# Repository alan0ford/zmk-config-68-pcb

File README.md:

## PCB 68 keyboard
PCB bluetooth mechanical keyboard.

- Case: in plywood handmade [(photo)](https://i.imgur.com/p45XYWJ.jpg)
- [PCB](https://imgur.com/a/tlV6TRd)
- Keycpas: CRP-X Parallel Worlds
- Switches: WS Jade POM linear 50 g
- MCU: SuperMini NRF52580 [(nice!nano compatible)](http://wiki.icbbuy.com/doku.php?id=developmentboard:nrf52840)
- Soundcheck ([here](https://vimeo.com/914201447?share=copy))

Inspired by Ikki 68:

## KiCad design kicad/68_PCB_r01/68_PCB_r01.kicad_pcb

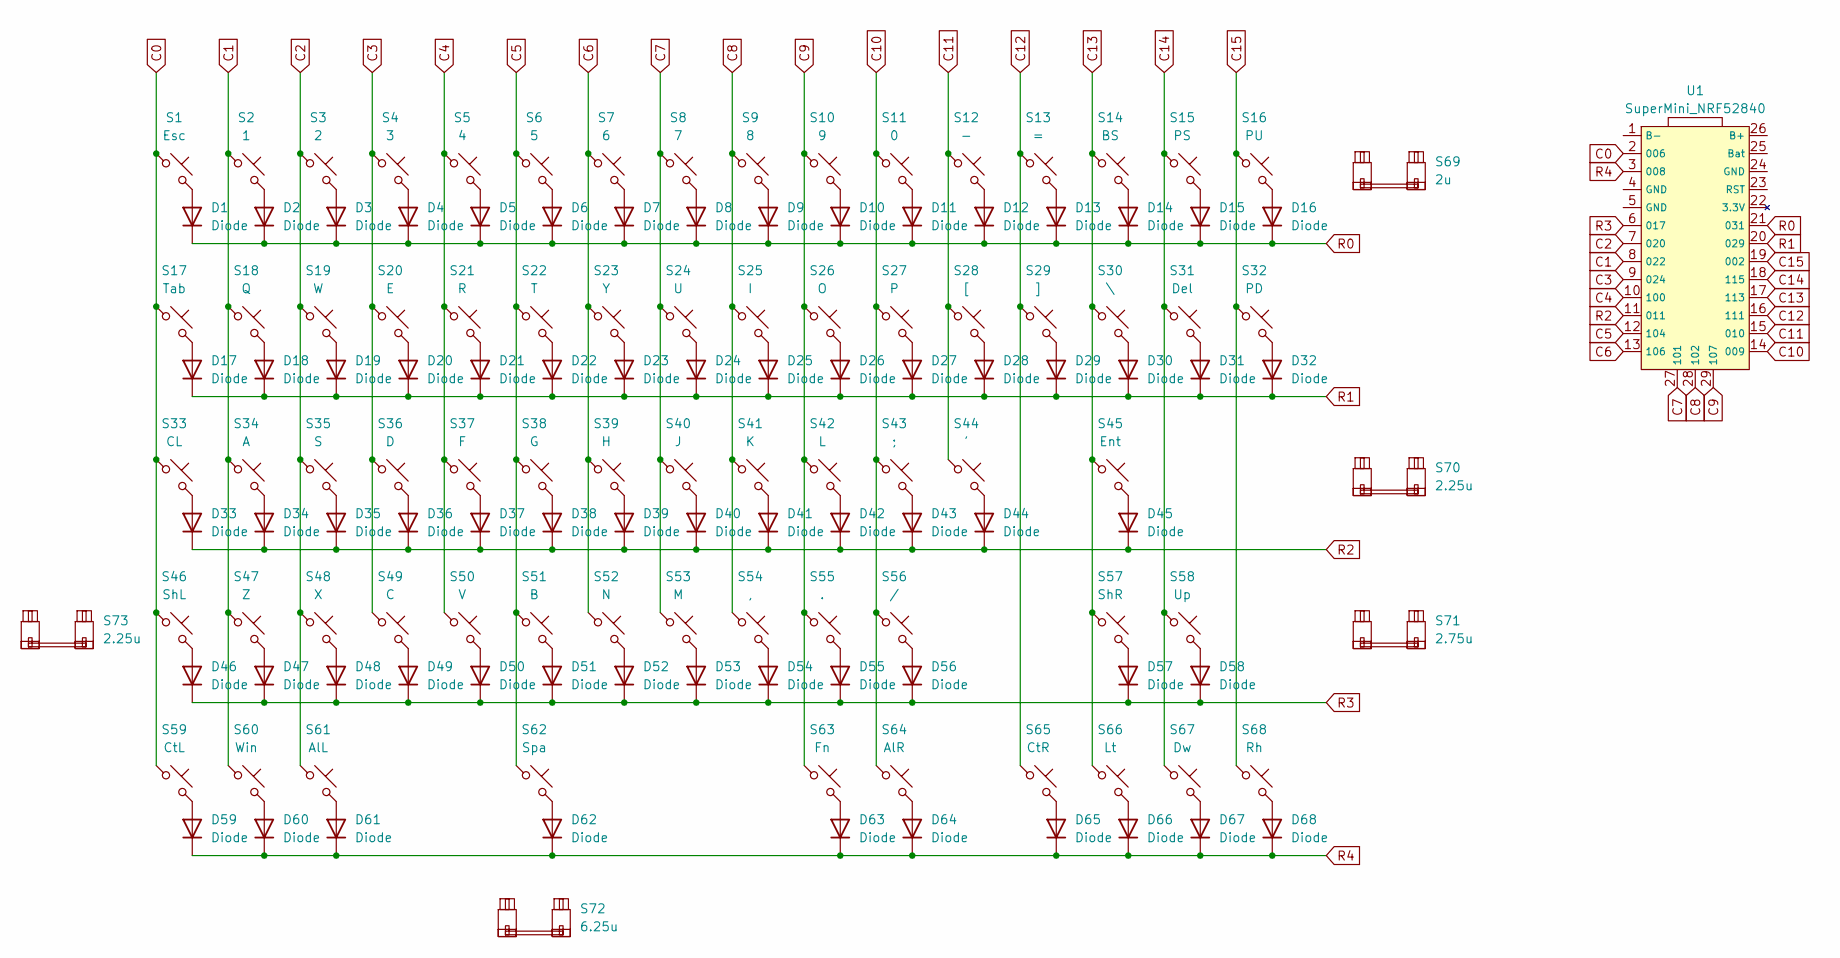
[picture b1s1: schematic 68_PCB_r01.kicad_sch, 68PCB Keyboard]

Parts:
D1, D2, D3, D4, D5, D6, D7, D8, D9, D10, D11, D12, D13, D14, D15, D16, D17, D18, D19, D20, D21, D22, D23, D24, D25, D26, D27, D28, D29, D30, D31, D32, D33, D34, D35, D36, D37, D38, D39, D40, D41, D42, D43, D44, D45, D46, D47, D48, D49, D50, D51, D52, D53, D54, D55, D56, D57, D58, D59, D60, D61, D62, D63, D64, D65, D66, D67, D68: Diode; Diode_DO-35
S1: Esc; MX_PCB_1.00u
S2: 1; MX_PCB_1.00u
S3: 2; MX_PCB_1.00u
S4: 3; MX_PCB_1.00u
S5: 4; MX_PCB_1.00u
S6: 5; MX_PCB_1.00u
S7: 6; MX_PCB_1.00u
S8: 7; MX_PCB_1.00u
S9: 8; MX_PCB_1.00u
S10: 9; MX_PCB_1.00u
S11: 0; MX_PCB_1.00u
S12: -; MX_PCB_1.00u
S13: =; MX_PCB_1.00u
S14: BS; MX_PCB_2.00u
S15: PS; MX_PCB_1.00u
S16: PU; MX_PCB_1.00u
S17: Tab; MX_PCB_1.50u
S18: Q; MX_PCB_1.00u
S19: W; MX_PCB_1.00u
S20: E; MX_PCB_1.00u
S21: R; MX_PCB_1.00u
S22: T; MX_PCB_1.00u
S23: Y; MX_PCB_1.00u
S24: U; MX_PCB_1.00u
S25: I; MX_PCB_1.00u
S26: O; MX_PCB_1.00u
S27: P; MX_PCB_1.00u
S28: [; MX_PCB_1.00u
S29: ]; MX_PCB_1.00u
S30: \; MX_PCB_1.50u
S31: Del; MX_PCB_1.00u
S32: PD; MX_PCB_1.00u
S33: CL; MX_PCB_1.75u
S34: A; MX_PCB_1.00u
S35: S; MX_PCB_1.00u
S36: D; MX_PCB_1.00u
S37: F; MX_PCB_1.00u
S38: G; MX_PCB_1.00u
S39: H; MX_PCB_1.00u
S40: J; MX_PCB_1.00u
S41: K; MX_PCB_1.00u
S42: L; MX_PCB_1.00u
S43: ;; MX_PCB_1.00u
S44: '; MX_PCB_1.00u
S45: Ent; MX_PCB_2.25u
S46: ShL; MX_PCB_2.25u
S47: Z; MX_PCB_1.00u
S48: X; MX_PCB_1.00u
S49: C; MX_PCB_1.00u
S50: V; MX_PCB_1.00u
S51: B; MX_PCB_1.00u
S52: N; MX_PCB_1.00u
S53: M; MX_PCB_1.00u
S54: ,; MX_PCB_1.00u
S55: .; MX_PCB_1.00u
S56: /; MX_PCB_1.00u
S57: ShR; MX_PCB_2.75u
S58: Up; MX_PCB_1.00u
S59: CtL; MX_PCB_1.25u
S60: Win; MX_PCB_1.25u
S61: AlL; MX_PCB_1.25u
S62: Spa; MX_PCB_6.25u
S63: Fn; MX_PCB_1.25u
S64: AlR; MX_PCB_1.25u
S65: CtR; MX_PCB_1.25u
S66: Lt; MX_PCB_1.00u
S67: Dw; MX_PCB_1.00u
S68: Rh; MX_PCB_1.00u
S69: 2u; STAB_MX_2u
S70, S73: 2.25u; STAB_MX_2.25u
S71: 2.75u; STAB_MX_2.75u
S72: 6.25u; STAB_MX_6.25u
U1: SuperMini_NRF52840; SuperMini NRF52840

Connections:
C0: S1.1, S17.1, S33.1, S46.1, S59.1, U1.2 (006)
C1: S2.1, S18.1, S34.1, S47.1, S60.1, U1.8 (022)
C2: S3.1, S19.1, S35.1, S48.1, S61.1, U1.7 (020)
C3: S4.1, S20.1, S36.1, S49.1, U1.9 (024)
C4: S5.1, S21.1, S37.1, S50.1, U1.10 (100)
C5: S6.1, S22.1, S38.1, S51.1, S62.1, U1.12 (104)
C6: S7.1, S23.1, S39.1, S52.1, U1.13 (106)
C7: S8.1, S24.1, S40.1, S53.1, U1.27 (101)
C8: S9.1, S25.1, S41.1, S54.1, U1.28 (102)
C9: S10.1, S26.1, S42.1, S55.1, S63.1, U1.29 (107)
C10: S11.1, S27.1, S43.1, S56.1, S64.1, U1.14 (009)
C11: S12.1, S28.1, S44.1, U1.15 (010)
C12: S13.1, S29.1, S65.1, U1.16 (111)
C13: S14.1, S30.1, S45.1, S57.1, S66.1, U1.17 (113)
C14: S15.1, S31.1, S58.1, S67.1, U1.18 (115)
C15: S16.1, S32.1, S68.1, U1.19 (002)
unnamed: D1.2 (A), S1.2
unnamed: D2.2 (A), S2.2
unnamed: D3.2 (A), S3.2
unnamed: D4.2 (A), S4.2
unnamed: D5.2 (A), S5.2
unnamed: D6.2 (A), S6.2
unnamed: D7.2 (A), S7.2
unnamed: D8.2 (A), S8.2
unnamed: D9.2 (A), S9.2
unnamed: D10.2 (A), S10.2
unnamed: D11.2 (A), S11.2
unnamed: D12.2 (A), S12.2
unnamed: D13.2 (A), S13.2
unnamed: D14.2 (A), S14.2
unnamed: D15.2 (A), S15.2
unnamed: D16.2 (A), S16.2
unnamed: D17.2 (A), S17.2
unnamed: D18.2 (A), S18.2
unnamed: D19.2 (A), S19.2
unnamed: D20.2 (A), S20.2
unnamed: D21.2 (A), S21.2
unnamed: D22.2 (A), S22.2
unnamed: D23.2 (A), S23.2
unnamed: D24.2 (A), S24.2
unnamed: D25.2 (A), S25.2
unnamed: D26.2 (A), S26.2
unnamed: D27.2 (A), S27.2
unnamed: D28.2 (A), S28.2
unnamed: D29.2 (A), S29.2
unnamed: D30.2 (A), S30.2
unnamed: D31.2 (A), S31.2
unnamed: D32.2 (A), S32.2
unnamed: D33.2 (A), S33.2
unnamed: D34.2 (A), S34.2
unnamed: D35.2 (A), S35.2
unnamed: D36.2 (A), S36.2
unnamed: D37.2 (A), S37.2
unnamed: D38.2 (A), S38.2
unnamed: D39.2 (A), S39.2
unnamed: D40.2 (A), S40.2
unnamed: D41.2 (A), S41.2
unnamed: D42.2 (A), S42.2
unnamed: D43.2 (A), S43.2
unnamed: D44.2 (A), S44.2
unnamed: D45.2 (A), S45.2
unnamed: D46.2 (A), S46.2
unnamed: D47.2 (A), S47.2
unnamed: D48.2 (A), S48.2
unnamed: D49.2 (A), S49.2
unnamed: D50.2 (A), S50.2
unnamed: D51.2 (A), S51.2
unnamed: D52.2 (A), S52.2
unnamed: D53.2 (A), S53.2
unnamed: D54.2 (A), S54.2
unnamed: D55.2 (A), S55.2
unnamed: D56.2 (A), S56.2
unnamed: D57.2 (A), S57.2
unnamed: D58.2 (A), S58.2
unnamed: D59.2 (A), S59.2
unnamed: D60.2 (A), S60.2
unnamed: D61.2 (A), S61.2
unnamed: D62.2 (A), S62.2
unnamed: D63.2 (A), S63.2
unnamed: D64.2 (A), S64.2
unnamed: D65.2 (A), S65.2
unnamed: D66.2 (A), S66.2
unnamed: D67.2 (A), S67.2
unnamed: D68.2 (A), S68.2
R0: D1.1 (K), D2.1 (K), D3.1 (K), D4.1 (K), D5.1 (K), D6.1 (K), D7.1 (K), D8.1 (K), D9.1 (K), D10.1 (K), D11.1 (K), D12.1 (K), D13.1 (K), D14.1 (K), D15.1 (K), D16.1 (K), U1.21 (031)
R1: D17.1 (K), D18.1 (K), D19.1 (K), D20.1 (K), D21.1 (K), D22.1 (K), D23.1 (K), D24.1 (K), D25.1 (K), D26.1 (K), D27.1 (K), D28.1 (K), D29.1 (K), D30.1 (K), D31.1 (K), D32.1 (K), U1.20 (029)
R2: D33.1 (K), D34.1 (K), D35.1 (K), D36.1 (K), D37.1 (K), D38.1 (K), D39.1 (K), D40.1 (K), D41.1 (K), D42.1 (K), D43.1 (K), D44.1 (K), D45.1 (K), U1.11
R3: D46.1 (K), D47.1 (K), D48.1 (K), D49.1 (K), D50.1 (K), D51.1 (K), D52.1 (K), D53.1 (K), D54.1 (K), D55.1 (K), D56.1 (K), D57.1 (K), D58.1 (K), U1.6 (017)
R4: D59.1 (K), D60.1 (K), D61.1 (K), D62.1 (K), D63.1 (K), D64.1 (K), D65.1 (K), D66.1 (K), D67.1 (K), D68.1 (K), U1.3 (008)

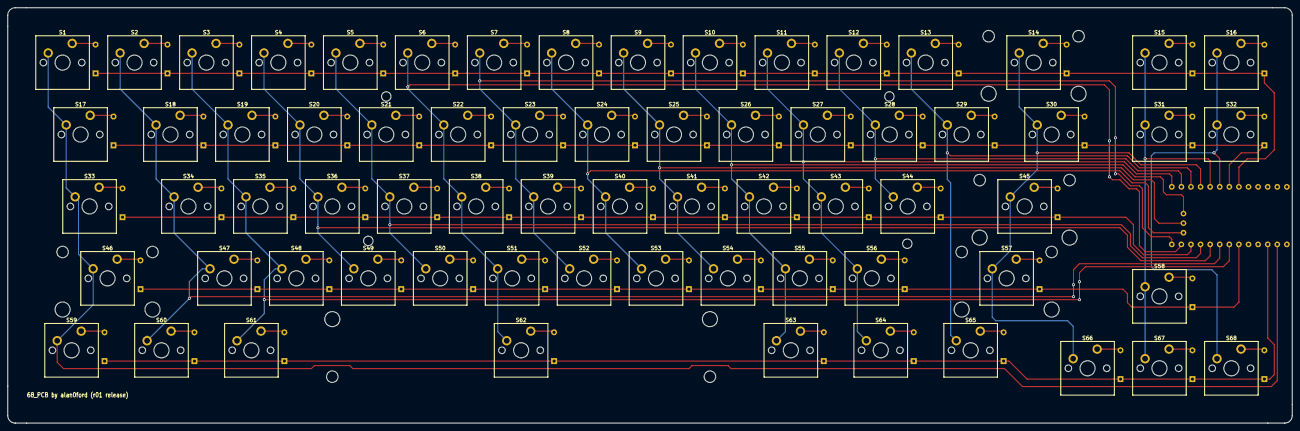
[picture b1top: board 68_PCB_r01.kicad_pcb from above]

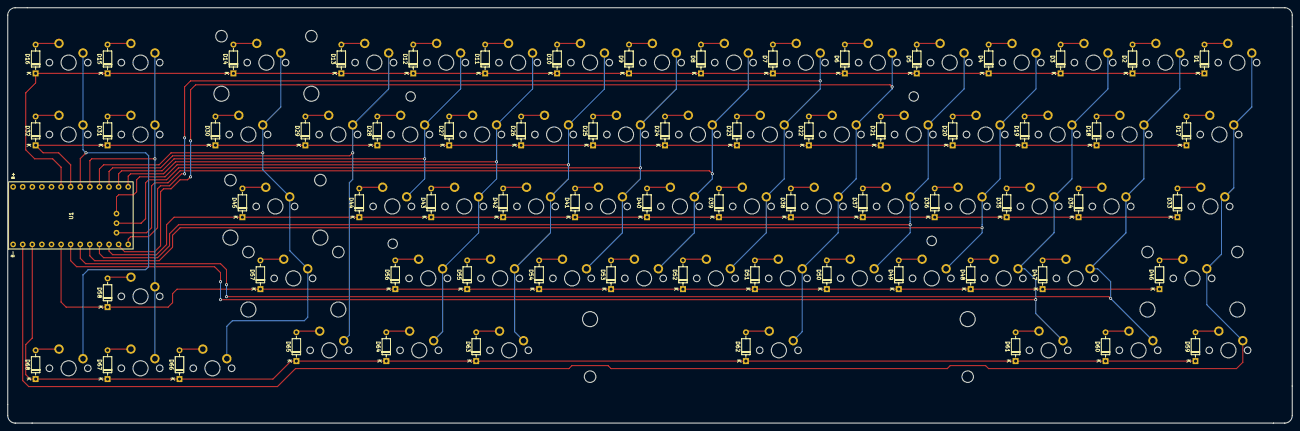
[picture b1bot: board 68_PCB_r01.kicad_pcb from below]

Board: 2 copper layers, 340.2 x 110.0 mm, 142 parts (69 on the bottom side), 89 nets.

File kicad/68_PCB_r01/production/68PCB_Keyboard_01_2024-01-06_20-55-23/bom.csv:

Designator,Footprint,Quantity,Value,LCSC Part #
"D1, D10, D11, D12, D13, D14, D15, D16, D17, D18, D19, D2, D20, D21, D22, D23, D24, D25, D26, D27, D28, D29, D3, D30, D31, D32, D33, D34, D35, D36, D37, D38, D39, D4, D40, D41, D42, D43, D44, D45, D46, D47, D48, D49, D5, D50, D51, D52, D53, D54, D55, D56, D57, D58, D59, D6, D60, D61, D62, D63, D64, D65, D66, D67, D68, D7, D8, D9",Diode_DO-35,68,Diode,
S1,MX_PCB_1.00u,1,Esc,
S10,MX_PCB_1.00u,1,9,
S11,MX_PCB_1.00u,1,0,
S12,MX_PCB_1.00u,1,-,
S13,MX_PCB_1.00u,1,=,
S14,MX_PCB_2.00u,1,BS,
S15,MX_PCB_1.00u,1,PS,
S16,MX_PCB_1.00u,1,PU,
S17,MX_PCB_1.50u,1,Tab,
S18,MX_PCB_1.00u,1,Q,
S19,MX_PCB_1.00u,1,W,
S2,MX_PCB_1.00u,1,1,
S20,MX_PCB_1.00u,1,E,
S21,MX_PCB_1.00u,1,R,
S22,MX_PCB_1.00u,1,T,
S23,MX_PCB_1.00u,1,Y,
S24,MX_PCB_1.00u,1,U,
S25,MX_PCB_1.00u,1,I,
S26,MX_PCB_1.00u,1,O,
S27,MX_PCB_1.00u,1,P,
S28,MX_PCB_1.00u,1,[,
S29,MX_PCB_1.00u,1,],
S3,MX_PCB_1.00u,1,2,
S30,MX_PCB_1.50u,1,\,
S31,MX_PCB_1.00u,1,Del,
S32,MX_PCB_1.00u,1,PD,
S33,MX_PCB_1.75u,1,CL,
S34,MX_PCB_1.00u,1,A,
S35,MX_PCB_1.00u,1,S,
S36,MX_PCB_1.00u,1,D,
S37,MX_PCB_1.00u,1,F,
S38,MX_PCB_1.00u,1,G,
S39,MX_PCB_1.00u,1,H,
S4,MX_PCB_1.00u,1,3,
S40,MX_PCB_1.00u,1,J,
S41,MX_PCB_1.00u,1,K,
S42,MX_PCB_1.00u,1,L,
S43,MX_PCB_1.00u,1,;,
S44,MX_PCB_1.00u,1,',
S45,MX_PCB_2.25u,1,Ent,
S46,MX_PCB_2.25u,1,ShL,
S47,MX_PCB_1.00u,1,Z,
S48,MX_PCB_1.00u,1,X,
S49,MX_PCB_1.00u,1,C,
S5,MX_PCB_1.00u,1,4,
S50,MX_PCB_1.00u,1,V,
S51,MX_PCB_1.00u,1,B,
S52,MX_PCB_1.00u,1,N,
S53,MX_PCB_1.00u,1,M,
S54,MX_PCB_1.00u,1,",",
S55,MX_PCB_1.00u,1,.,
S56,MX_PCB_1.00u,1,/,
S57,MX_PCB_2.75u,1,ShR,
S58,MX_PCB_1.00u,1,Up,
S59,MX_PCB_1.25u,1,CtL,
S6,MX_PCB_1.00u,1,5,
S60,MX_PCB_1.25u,1,Win,
S61,MX_PCB_1.25u,1,AlL,
S62,MX_PCB_6.25u,1,Spa,
S63,MX_PCB_1.25u,1,Fn,
S64,MX_PCB_1.25u,1,AlR,
S65,MX_PCB_1.25u,1,CtR,
S66,MX_PCB_1.00u,1,Lt,
S67,MX_PCB_1.00u,1,Dw,
S68,MX_PCB_1.00u,1,Rh,
S69,STAB_MX_2u,1,2u,
S7,MX_PCB_1.00u,1,6,
"S70, S73",STAB_MX_2.25u,2,2.25u,
S71,STAB_MX_2.75u,1,2.75u,
S72,STAB_MX_6.25u,1,6.25u,
S8,MX_PCB_1.00u,1,7,
S9,MX_PCB_1.00u,1,8,
U1,SuperMini NRF52840,1,SuperMini_NRF52840,

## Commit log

2024-01-07 shield_name
2024-01-08 base config
2024-01-09 defined keymap
2024-01-19 aggiunti file kicad
2024-01-23 Updated 68-pcb.keymap
2024-08-06 keycaps akko
2024-08-06 rinominato 68pcb
2024-11-08 new keymaps
2024-11-10 newest keymap
2025-10-27 Add battery printer behavior for 68pcb shield
    Introduces a custom ZMK behavior that types the current battery percentage with a label when activated. Adds the implementation, devicetree binding, and integrates the behavior into the 68pcb keymap.
2026-01-20 fix board name
